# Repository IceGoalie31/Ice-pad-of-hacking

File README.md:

# Ice-pad-of-hacking

---------------------------
Welcome! This is a repository for my hackpad submission for Hack Club, expect some weirdness in the design as this is my first time making a PCB.

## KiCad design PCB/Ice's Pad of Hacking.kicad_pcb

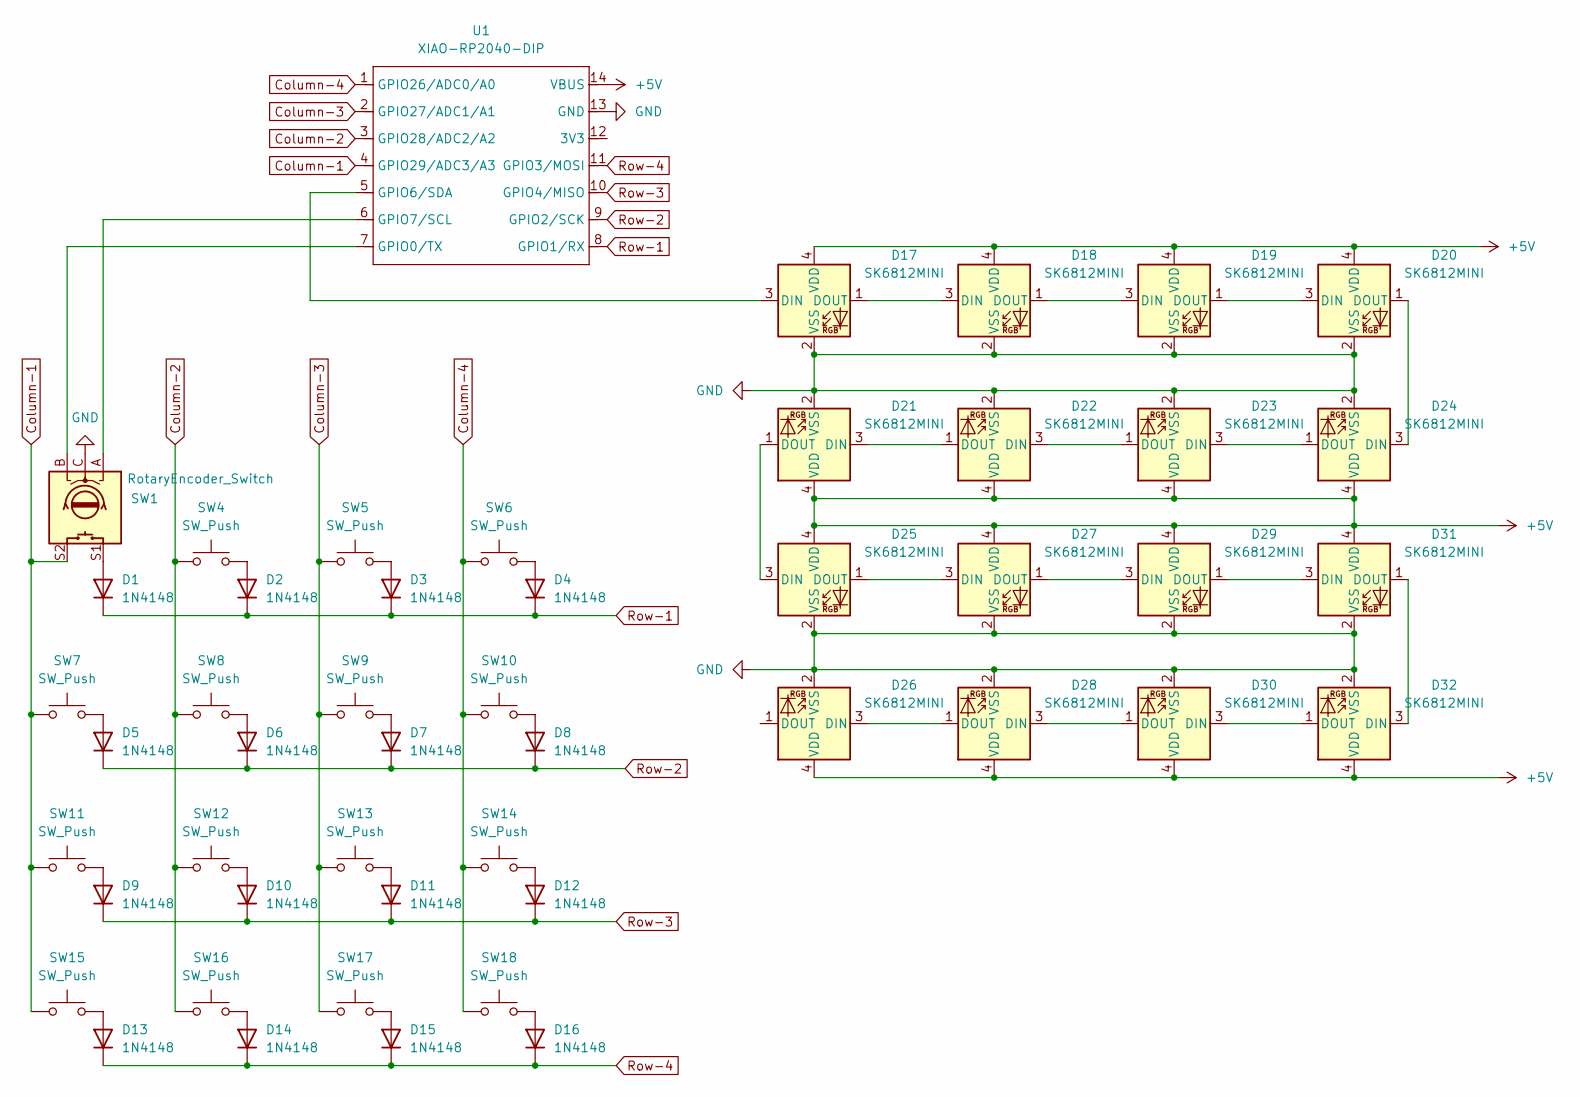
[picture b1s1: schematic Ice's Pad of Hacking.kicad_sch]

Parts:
D1, D2, D3, D4, D5, D6, D7, D8, D9, D10, D11, D12, D13, D14, D15, D16: 1N4148; D_DO-35_SOD27_P7.62mm_Horizontal
D17: SK6812MINI; LED_SK6812MINI_PLCC4_3.5x3.5mm_P1.75mm
D18, D19, D20, D21, D22, D23, D24, D25, D26, D27, D28, D29, D30, D31, D32: SK6812MINI; SK6812-MINI-E
SW1: RotaryEncoder_Switch; RotaryEncoder_Alps_EC11E-Switch_Vertical_H20mm
SW4, SW5, SW6, SW7, SW8, SW9, SW10, SW11, SW12, SW13, SW14, SW15, SW16, SW17, SW18: SW_Push; SW_Cherry_MX_1.00u_PCB
U1: XIAO-RP2040-DIP

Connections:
+5V: D17.4 (VDD), D18.4 (VDD), D19.4 (VDD), D20.4 (VDD), D21.4 (VDD), D22.4 (VDD), D23.4 (VDD), D24.4 (VDD), D25.4 (VDD), D26.4 (VDD), D27.4 (VDD), D28.4 (VDD), D29.4 (VDD), D30.4 (VDD), D31.4 (VDD), D32.4 (VDD), U1.14 (VBUS)
Column-1: SW1.S2, SW7.1, SW11.1, SW15.1, U1.4 (GPIO29/ADC3/A3)
Column-2: SW4.1, SW8.1, SW12.1, SW16.1, U1.3 (GPIO28/ADC2/A2)
Column-3: SW5.1, SW9.1, SW13.1, SW17.1, U1.2 (GPIO27/ADC1/A1)
Column-4: SW6.1, SW10.1, SW14.1, SW18.1, U1.1 (GPIO26/ADC0/A0)
GND: D17.2 (VSS), D18.2 (VSS), D19.2 (VSS), D20.2 (VSS), D21.2 (VSS), D22.2 (VSS), D23.2 (VSS), D24.2 (VSS), D25.2 (VSS), D26.2 (VSS), D27.2 (VSS), D28.2 (VSS), D29.2 (VSS), D30.2 (VSS), D31.2 (VSS), D32.2 (VSS), SW1.C, U1.13 (GND)
unnamed: D1.2 (A), SW1.S1
unnamed: D2.2 (A), SW4.2
unnamed: D3.2 (A), SW5.2
unnamed: D4.2 (A), SW6.2
unnamed: D5.2 (A), SW7.2
unnamed: D6.2 (A), SW8.2
unnamed: D7.2 (A), SW9.2
unnamed: D8.2 (A), SW10.2
unnamed: D9.2 (A), SW11.2
unnamed: D10.2 (A), SW12.2
unnamed: D11.2 (A), SW13.2
unnamed: D12.2 (A), SW14.2
unnamed: D13.2 (A), SW15.2
unnamed: D14.2 (A), SW16.2
unnamed: D15.2 (A), SW17.2
unnamed: D16.2 (A), SW18.2
unnamed: D17.3 (DIN), U1.5 (GPIO6/SDA)
unnamed: D17.1 (DOUT), D18.3 (DIN)
unnamed: D18.1 (DOUT), D19.3 (DIN)
unnamed: D19.1 (DOUT), D20.3 (DIN)
unnamed: D20.1 (DOUT), D24.3 (DIN)
unnamed: D21.3 (DIN), D22.1 (DOUT)
unnamed: D21.1 (DOUT), D25.3 (DIN)
unnamed: D22.3 (DIN), D23.1 (DOUT)
unnamed: D23.3 (DIN), D24.1 (DOUT)
unnamed: D25.1 (DOUT), D27.3 (DIN)
unnamed: D26.3 (DIN), D28.1 (DOUT)
unnamed: D27.1 (DOUT), D29.3 (DIN)
unnamed: D28.3 (DIN), D30.1 (DOUT)
unnamed: D29.1 (DOUT), D31.3 (DIN)
unnamed: D30.3 (DIN), D32.1 (DOUT)
unnamed: D31.1 (DOUT), D32.3 (DIN)
unnamed: SW1.B, U1.7 (GPIO0/TX)
unnamed: SW1.A, U1.6 (GPIO7/SCL)
Row-1: D1.1 (K), D2.1 (K), D3.1 (K), D4.1 (K), U1.8 (GPIO1/RX)
Row-2: D5.1 (K), D6.1 (K), D7.1 (K), D8.1 (K), U1.9 (GPIO2/SCK)
Row-3: D9.1 (K), D10.1 (K), D11.1 (K), D12.1 (K), U1.10 (GPIO4/MISO)
Row-4: D13.1 (K), D14.1 (K), D15.1 (K), D16.1 (K), U1.11 (GPIO3/MOSI)

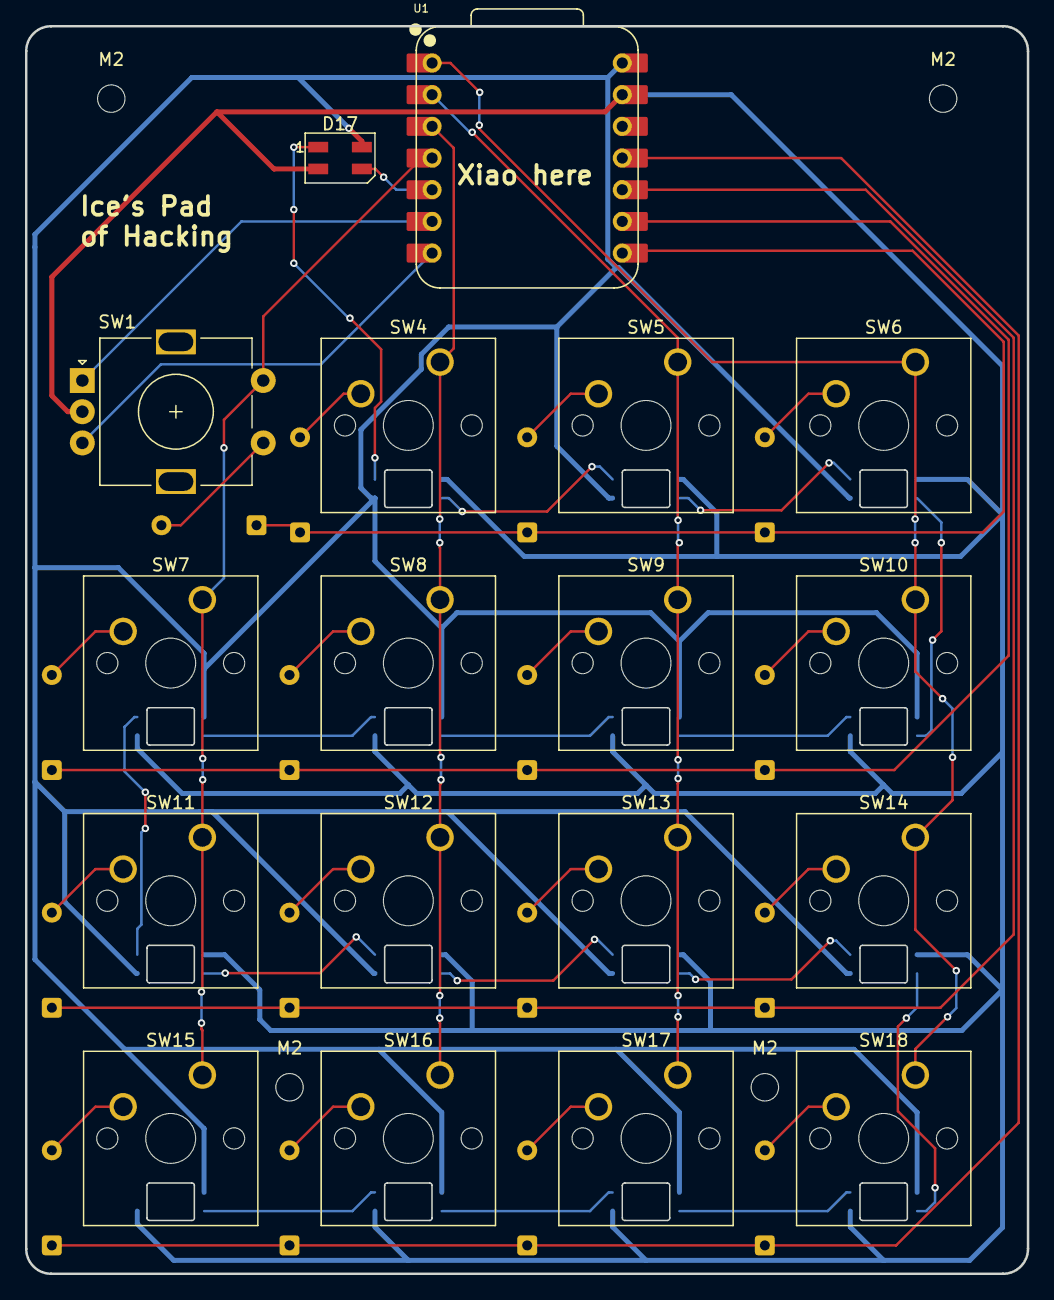
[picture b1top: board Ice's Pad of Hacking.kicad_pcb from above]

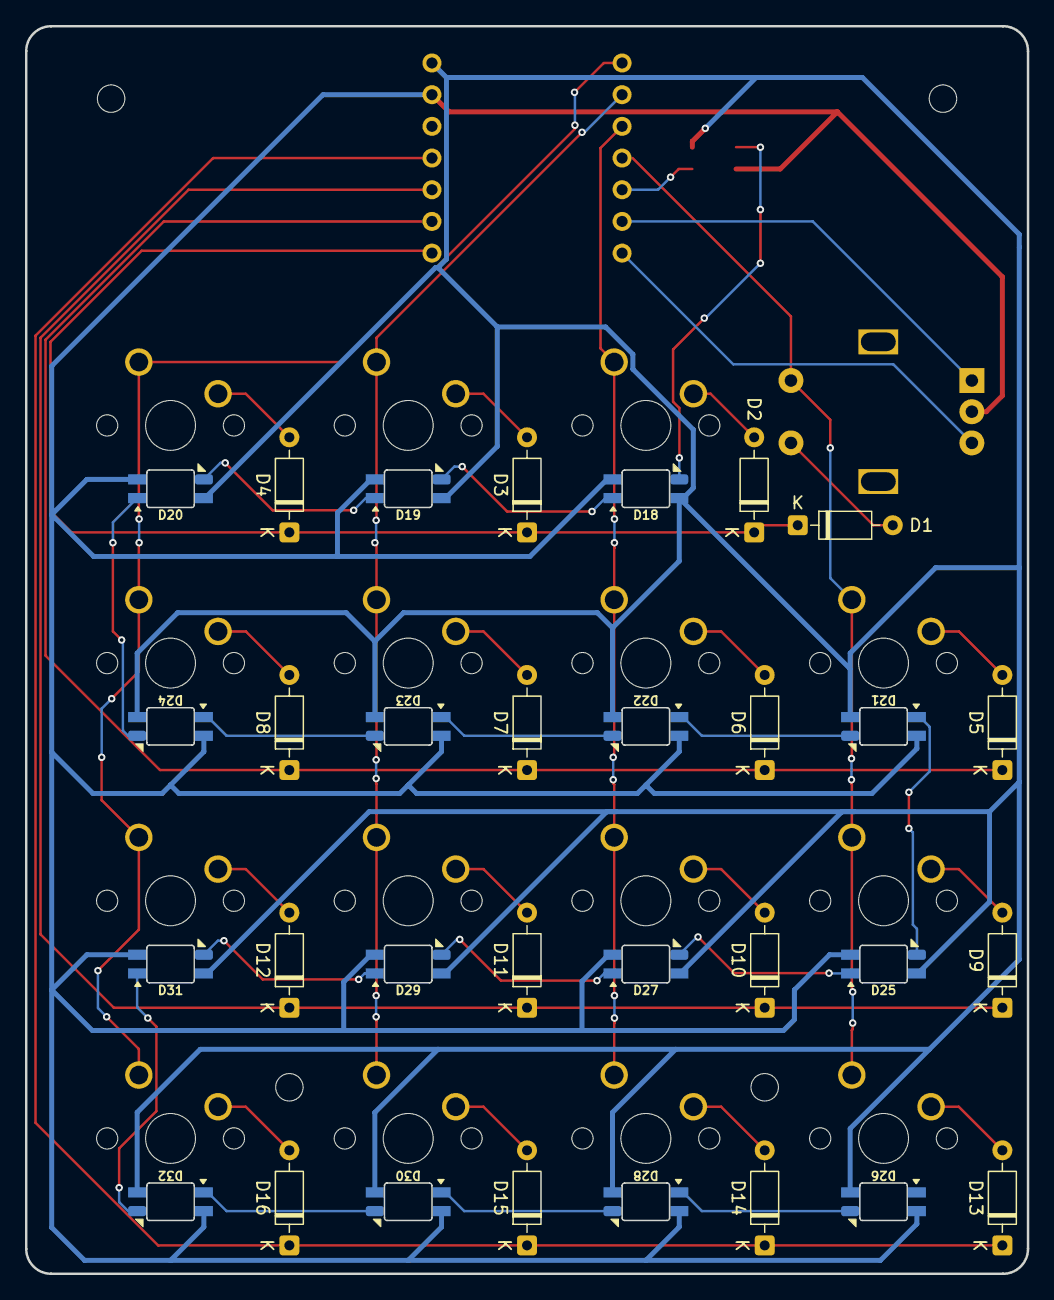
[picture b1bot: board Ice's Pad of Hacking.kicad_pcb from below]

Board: 2 copper layers, 80.3 x 100.0 mm, 53 parts (31 on the bottom side), 44 nets.

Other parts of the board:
M2, M2#2, M2#3, M2#4: MountingHole_2.2mm_M2

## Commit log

2025-07-24 Create createfolder
    Github's weird
2025-07-24 Update PCB mounting hole silkscreen
